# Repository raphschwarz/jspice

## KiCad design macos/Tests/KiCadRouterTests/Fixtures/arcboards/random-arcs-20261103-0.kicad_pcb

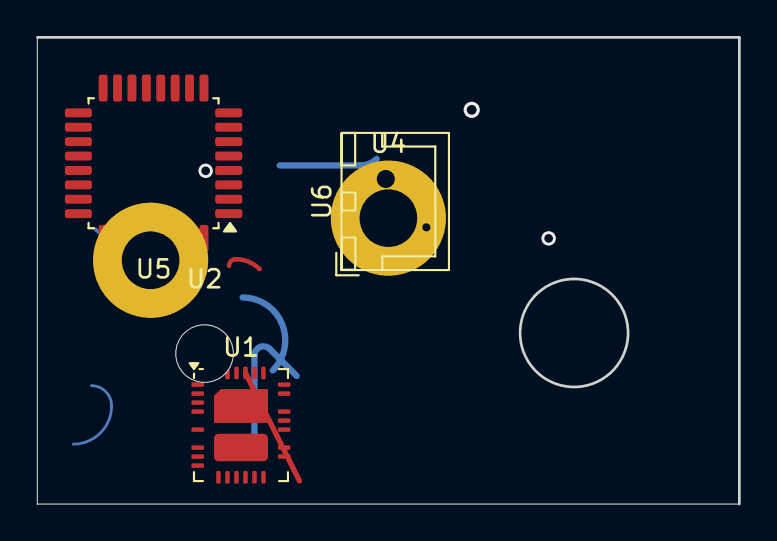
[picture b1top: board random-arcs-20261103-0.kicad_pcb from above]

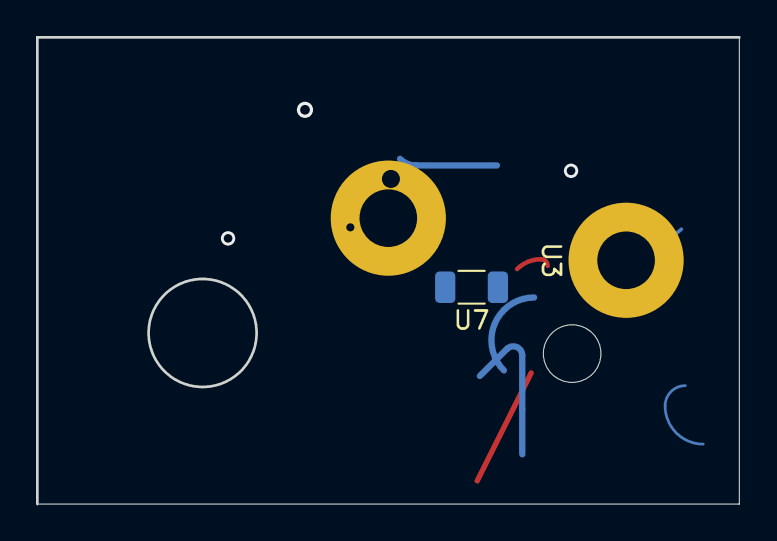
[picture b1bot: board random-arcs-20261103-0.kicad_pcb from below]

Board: 2 copper layers, 39.0 x 25.9 mm, 7 parts (2 on the bottom side), 9 nets.

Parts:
U1: Analog_QFN-28-36-2EP_5x6mm_P0.5mm
U2: MountingHole_3.2mm_M3
U3, U4: MountingHole_3.2mm_M3_Pad
U5: LQFP-32_7x7mm_P0.8mm
U6: JST_XH_B2B-XH-A_1x02_P2.50mm_Vertical
U7: R_1206_3216Metric

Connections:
/sub/clk: U1.1, U1.14, U1.27, U5.1, U5.14, U5.18, U5.30
D7: U1.20, U1.24, U5.3, U5.11, U5.20
D12: U1.9, U5.21, U5.25
GND: U1.6, U1.21, U4.1, U5.2, U5.6
N1: U1.2, U1.10, U1.16, U1.36, U5.9, U5.13, U5.17, U5.19, U5.31, U6.1
N2: U1.37, U3.1, U5.12, U5.32, U7.2
N3: U1.33, U5.4, U5.10
PWR1: U1.17, U1.25, U1.28, U1.38, U5.8, U5.27, U5.29
SIG2: U1.13, U5.26, U7.1

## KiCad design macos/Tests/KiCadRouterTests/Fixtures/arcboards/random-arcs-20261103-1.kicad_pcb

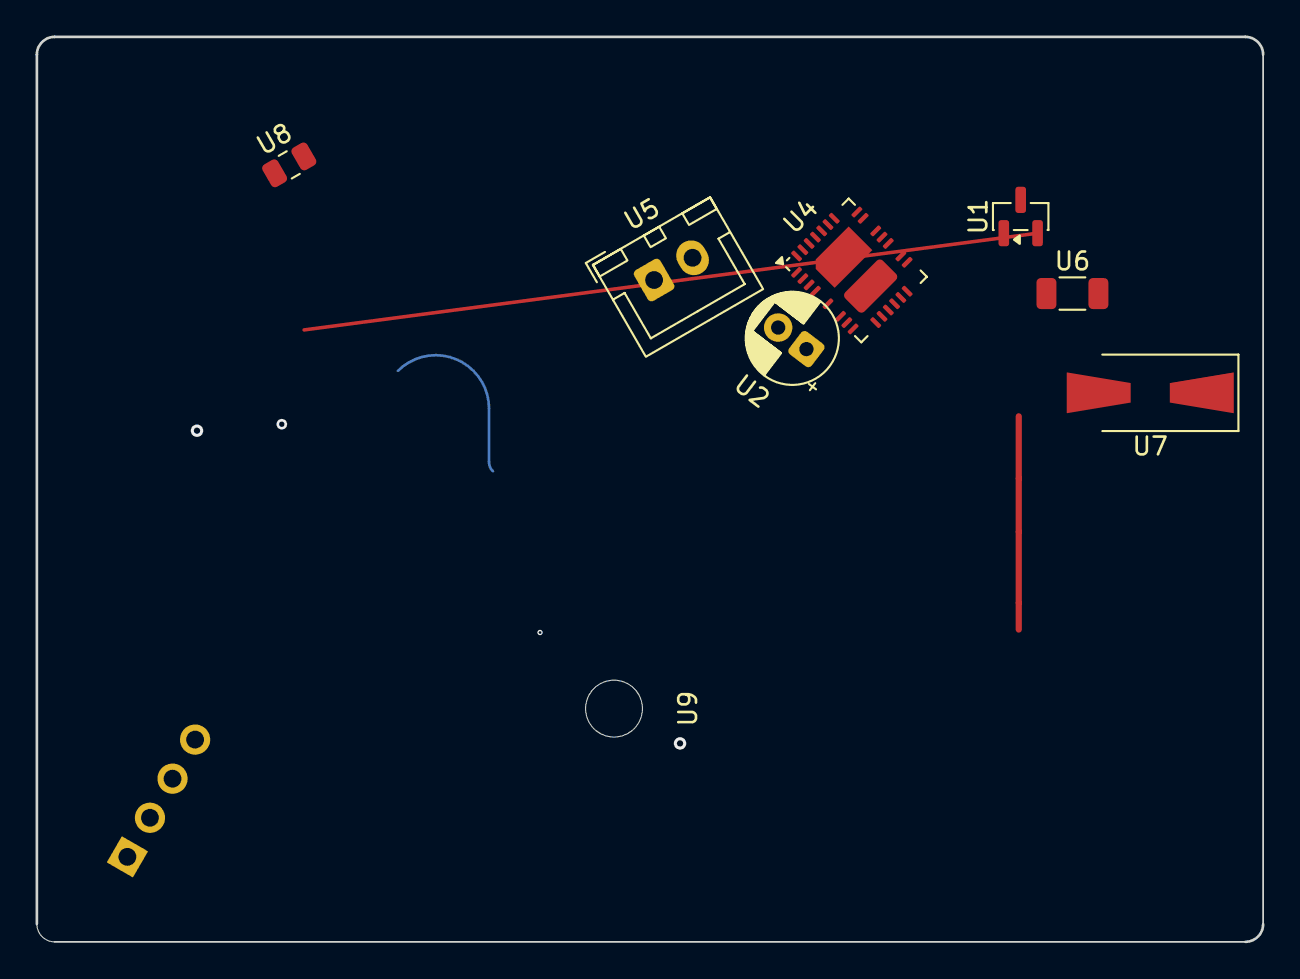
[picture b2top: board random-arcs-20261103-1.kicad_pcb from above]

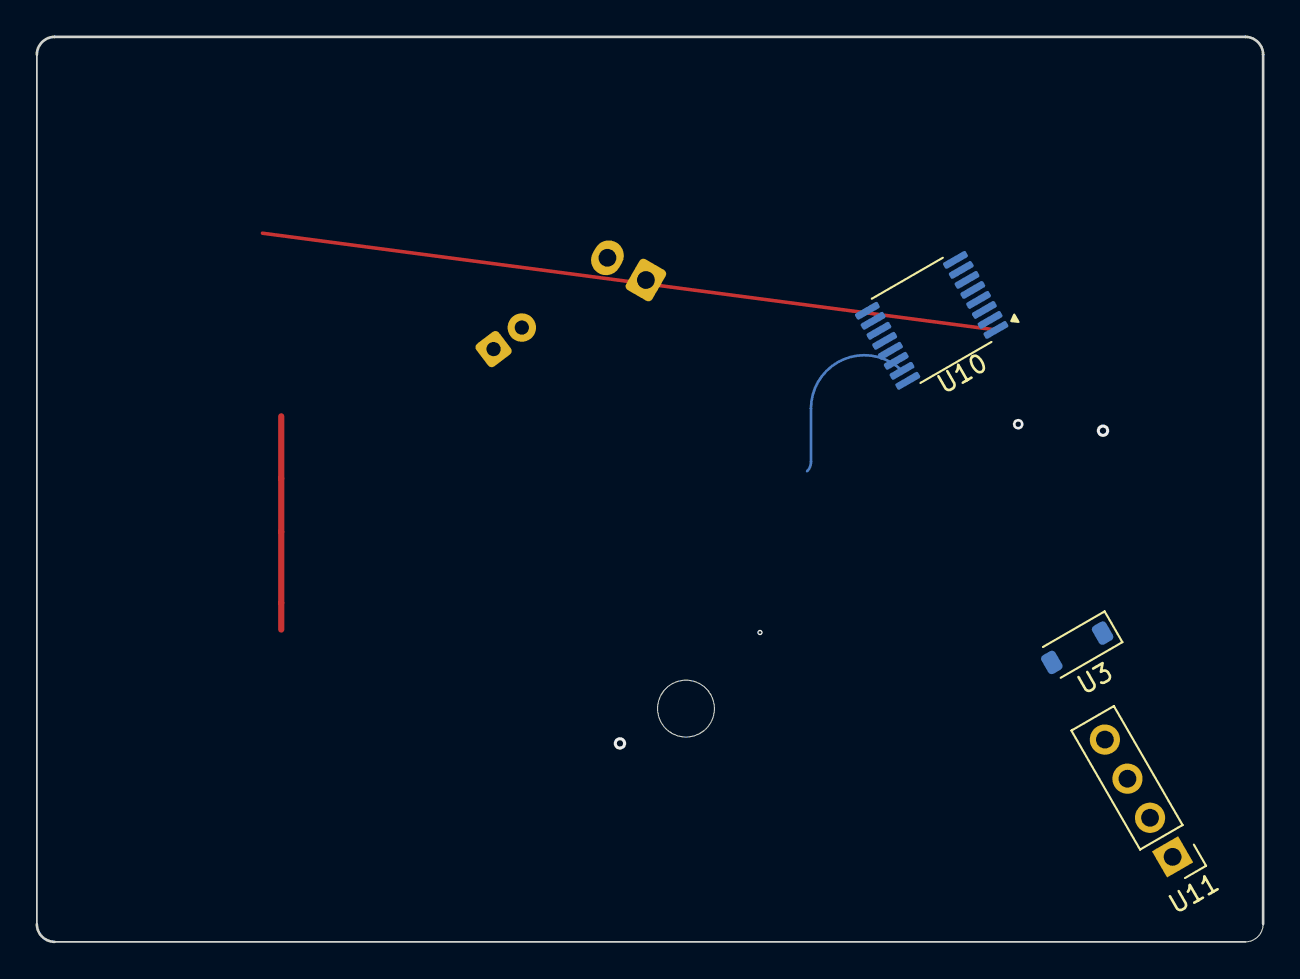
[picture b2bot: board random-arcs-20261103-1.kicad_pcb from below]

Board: 4 copper layers, 69.0 x 50.9 mm, 11 parts (3 on the bottom side), 5 nets.

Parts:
U1: SOT-23
U2: CP_Radial_D5.0mm_P2.00mm
U3: D_SOD-123
U4: Analog_QFN-28-36-2EP_5x6mm_P0.5mm
U5: JST_XH_B2B-XH-A_1x02_P2.50mm_Vertical
U6: R_1206_3216Metric
U7: D_SMA-SMB_Universal_Handsoldering
U8: C_0805_2012Metric
U9: MountingHole_3.2mm_M3
U10: TSSOP-16_4.4x5mm_P0.65mm
U11: PinHeader_1x04_P2.54mm_Vertical

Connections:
/sub/clk: U1.1, U1.2, U3.1, U3.2, U4.1, U4.6, U4.21, U6.2, U11.1, U11.2
D7: U2.2, U4.10, U4.38, U6.1, U7.1, U10.2, U10.4, U10.8, U10.13
GND: U1.3, U2.1, U4.2, U4.13, U4.15, U4.16, U4.30, U5.1, U10.10, U10.11, U10.15, U10.16
SIG1: U4.9, U4.14, U4.17, U4.20, U4.24, U4.28, U4.32, U7.2, U10.6, U10.9
SIG2: U4.4, U4.12, U4.25, U4.31, U4.33, U4.34, U4.37, U5.2, U8.2, U10.5, U10.7

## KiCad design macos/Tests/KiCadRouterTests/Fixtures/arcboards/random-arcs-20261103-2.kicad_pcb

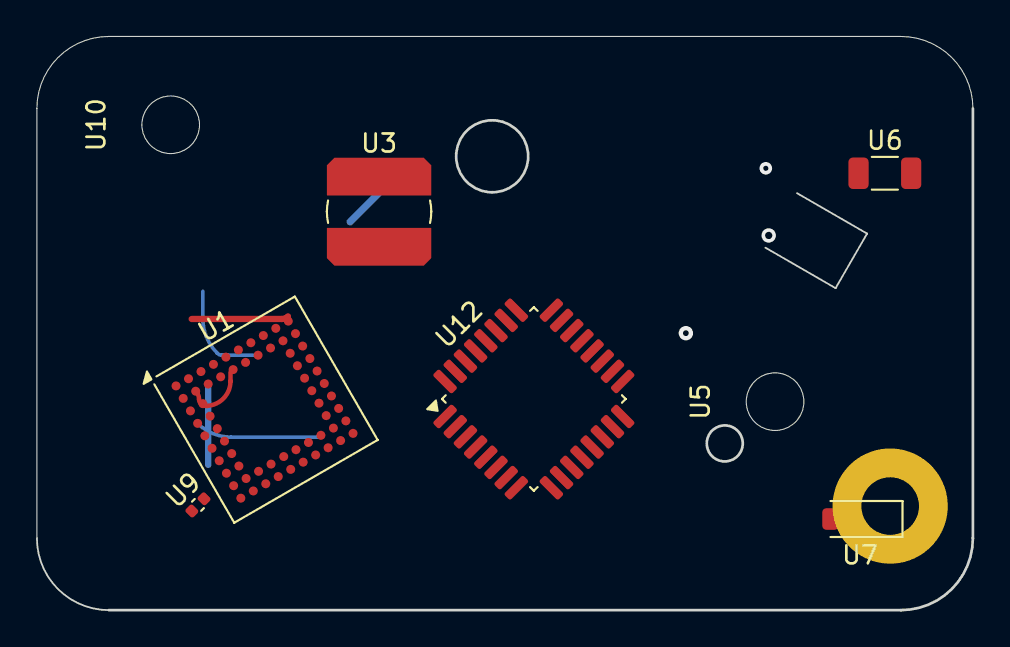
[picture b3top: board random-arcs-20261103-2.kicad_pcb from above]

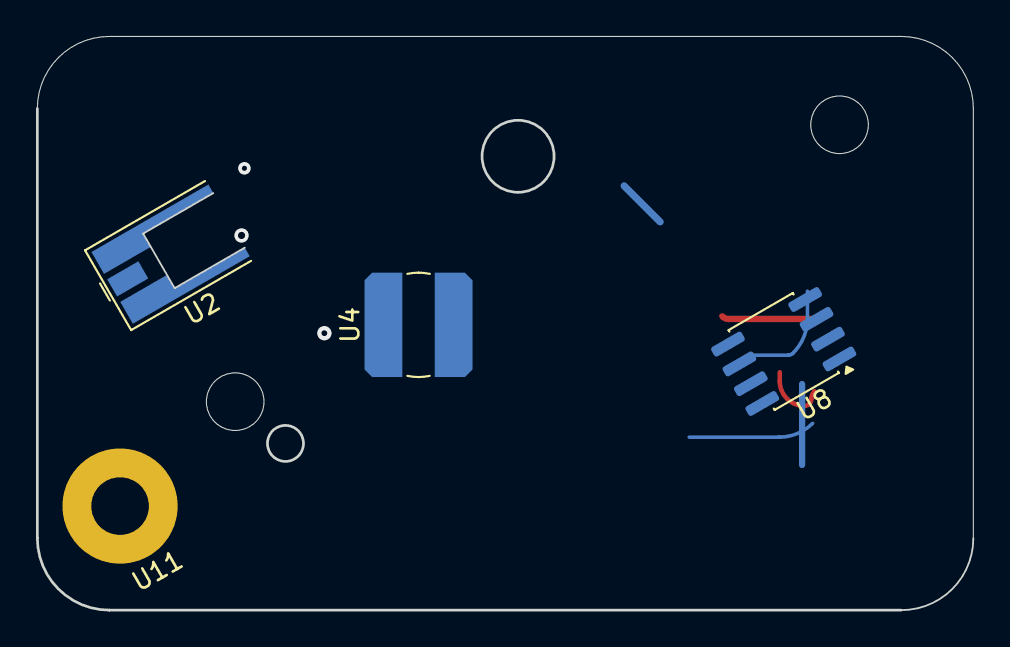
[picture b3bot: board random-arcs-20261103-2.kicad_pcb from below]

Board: 2 copper layers, 52.0 x 31.9 mm, 12 parts (4 on the bottom side), 12 nets.

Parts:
U1: BGA-64_9.0x9.0mm_Layout10x10_P0.8mm
U2: MMCX_Molex_73415-0961_Horizontal_0.8mm-PCB
U3, U4: L_Bourns_SDR0604
U5, U10: MountingHole_3.2mm_M3
U6: R_1206_3216Metric
U7: D_SOD-123
U8: SOIC-8_3.9x4.9mm_P1.27mm
U9: C_0402_1005Metric
U11: MountingHole_3.2mm_M3_Pad
U12: LQFP-32_7x7mm_P0.8mm

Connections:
/sub/clk: U1.B8, U1.K1, U2.2, U12.6, U12.13, U12.17, U12.28
D7: U1.A2, U1.A3, U1.C10, U1.D2, U1.E2, U2.2, U7.1, U8.8, U12.14, U12.15, U12.31
D12: U1.B2, U1.K7, U12.5, U12.16, U12.24
GND: U1.A9, U1.B9, U1.E9, U1.F2, U1.G1, U1.J4, U1.J10, U2.1, U3.1, U12.12, U12.21
N1: U1.D10, U1.E1, U1.J2, U1.J7, U1.J9, U4.2, U8.3
N2: U1.A7, U1.B4, U1.B5, U1.C9, U1.E10, U1.G2, U1.H9
N3: U1.D1, U1.F10, U1.K6, U8.7, U11.1, U12.7, U12.20, U12.26
PWR1: U1.A1, U1.A6, U1.B3, U1.B10, U1.F1, U1.G9, U1.H1, U1.K4, U9.2, U12.3
PWR_5V: U1.A10, U1.D9, U1.K8, U4.1, U7.2, U8.6
SIG1: U1.B6, U1.F9, U1.H10, U1.J1, U1.K5, U6.2, U12.8, U12.25, U12.29
SIG2: U1.B1, U1.B7, U1.H2, U1.J5, U12.22
VCC: U1.A4, U1.K2, U1.K9, U8.4, U12.4, U12.27, U12.32

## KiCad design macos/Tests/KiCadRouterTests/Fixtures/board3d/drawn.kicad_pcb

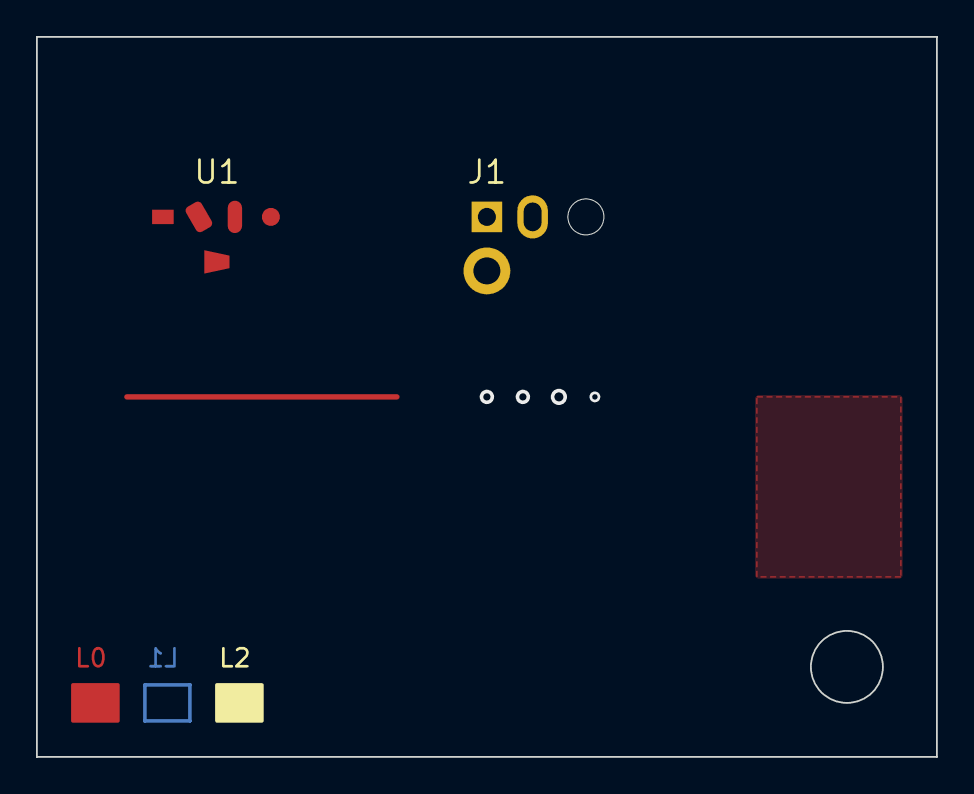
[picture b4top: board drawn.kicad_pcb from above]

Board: 4 copper layers, 50.0 x 40.0 mm, 3 parts (1 on the bottom side), 2 nets.

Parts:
J1: VJ1
Q1: VQ1
U1: VU1

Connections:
A: J1.1, Q1.1, U1.1
B: J1.2, Q1.2, U1.2
